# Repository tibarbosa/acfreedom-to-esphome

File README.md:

# AcFreedom To EspHome
Use ESPhome to have free access to Ac's without using the Acfreedom application. Use ESPhome plus Mqtt and homeassistant.

This project is just a simple hardware adapter to use with the project: [esphome_aux_ac_component](https://github.com/GrKoR/esphome_aux_ac_component)

Pictures
-------------------

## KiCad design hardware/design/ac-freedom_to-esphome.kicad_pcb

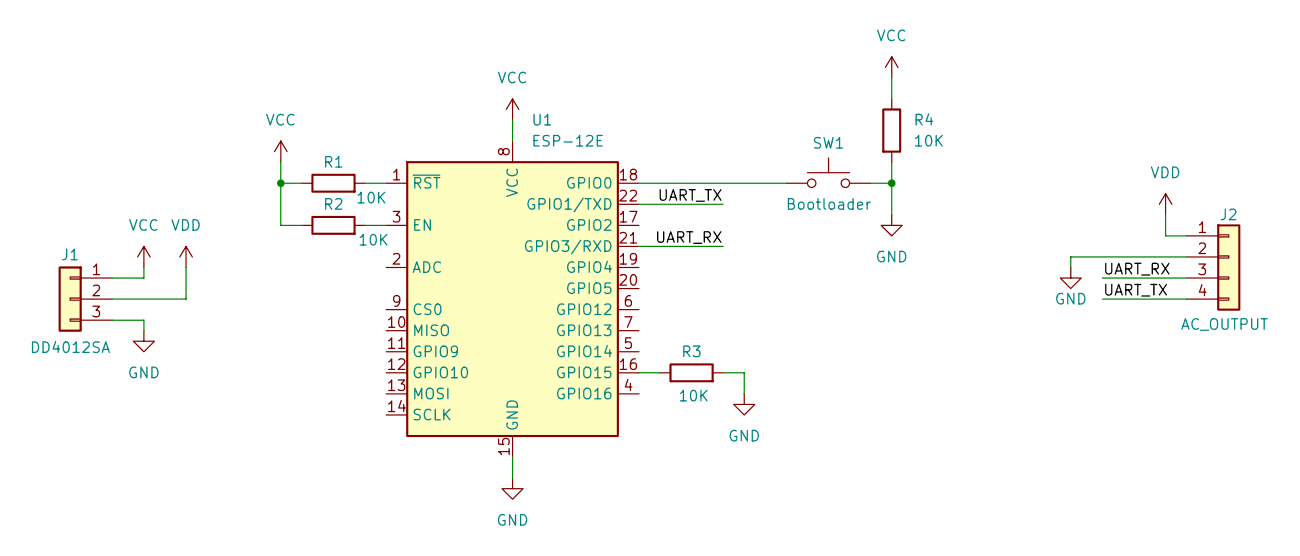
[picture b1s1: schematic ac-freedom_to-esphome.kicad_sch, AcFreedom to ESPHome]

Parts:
J1: DD4012SA
J2: AC_OUTPUT; PinHeader_1x04_P2.54mm_Vertical
R1, R2, R3, R4: 10K; R_0603_1608Metric
SW1: Bootloader; SW_PUSH_6mm
U1: ESP-12E

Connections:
/UART_RX: J2.3, U1.21 (GPIO3/RXD)
/UART_TX: J2.4, U1.22 (GPIO1/TXD)
GND: J1.3, J2.2, R3.2, R4.2, SW1.2, U1.15 (GND)
unnamed: R2.2, U1.3 (EN)
unnamed: SW1.1, U1.18 (GPIO0)
unnamed: R3.1, U1.16 (GPIO15)
unnamed: R1.2, U1.1 (~RST)
VCC: J1.1, R1.1, R2.1, R4.1, U1.8 (VCC)
VDD: J1.2, J2.1

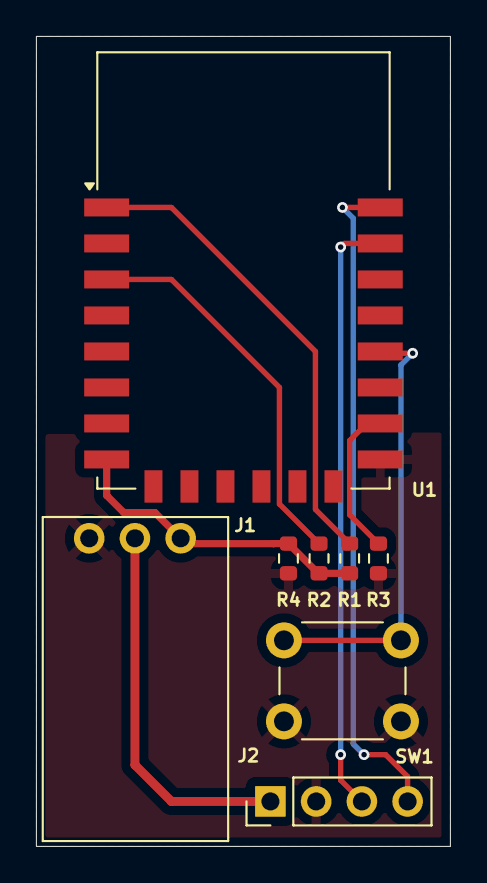
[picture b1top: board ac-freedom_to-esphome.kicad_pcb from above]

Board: 2 copper layers, 23.0 x 45.0 mm, 8 parts (0 on the bottom side), 9 nets.

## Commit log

2024-10-25 [hardware] Add first hardware design version
